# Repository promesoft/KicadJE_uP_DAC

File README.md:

# KicadJE_uP_DAC
Eurorack DAC output

# Purpose
Use for DDS/DCO - LFO - ADSR - Effects unit

# Status - Preliminary mounted
## Initial 
| Stage  | Detail | Status |
| ------------- | ------------- | ------------- |
| create material  | sch/pcb | OK  |
| | gerber | OK |
| production  |   | ok |
|  | produced | ok |
|  | delivered | ok |
## Preliminary validation
| Test  | Detail | Status |
| ------------- | ------------- | ------------- |
| Initial Inspection | | OK |
| Initial Technical Test | ATMega32A DAC | ADC not working due to GND conn to Aref |
| Initial Technical Test | STM32 DAC |  |
| Initial Technical Test | VCO555 | Initial version not oscillating - add 270R across C603 to make it work |
|  |  | TL074 warm |
| Initial Product Test | ATMega32A DAC |  |
| Initial Product Test | STM32 DAC |  |
| Initial Product Test | VCO555 |  |
| Power Draw | ATMega32A DAC | Proto - no DAC: 2mA -12V, 2mA +12V, 30mA +5V |
| Power Draw | STM32 DAC |  |
| Power Draw | VCO555 |  |

## Secondary validation
| Test  | Detail | Status |
| ------------- | ------------- |------------- |
| Product Test |  | |
| Product Test |  |  |
| Quality | | |
| Quality | | |
| Long Term Product Test |  |  |
| Power Draw | ATMega32A DAC |  |
| Power Draw | STM32 DAC |  |
| Power Draw | VCO555 |  |

## Errata
### Errata - VCO 555
1 - No oscillation fixed by replacing C603 w resistor (tested w 270R)
### Errata - ADSR Mega32
1 - ADC not working due to GND conn to Aref
### Errata - STM32 DAC

## Issues and Notes
### VCO 555

### ADSR Mega32
ADC not fast enough for audio

### STM32 DAC

# Pictures

# Other components

# Inspiration
## ATMega 32A
https://github.com/MCUdude/MightyCore
## STM32

## Simple 555 VCO

### Own Projects
https://github.com/promesoft/KicadFormantVCO

https://github.com/promesoft/KicadJE_LFO_1

### Intro about 555
https://www.electronics-tutorials.ws/waveforms/555_oscillator.html

### Thomas Henry 555 VCO

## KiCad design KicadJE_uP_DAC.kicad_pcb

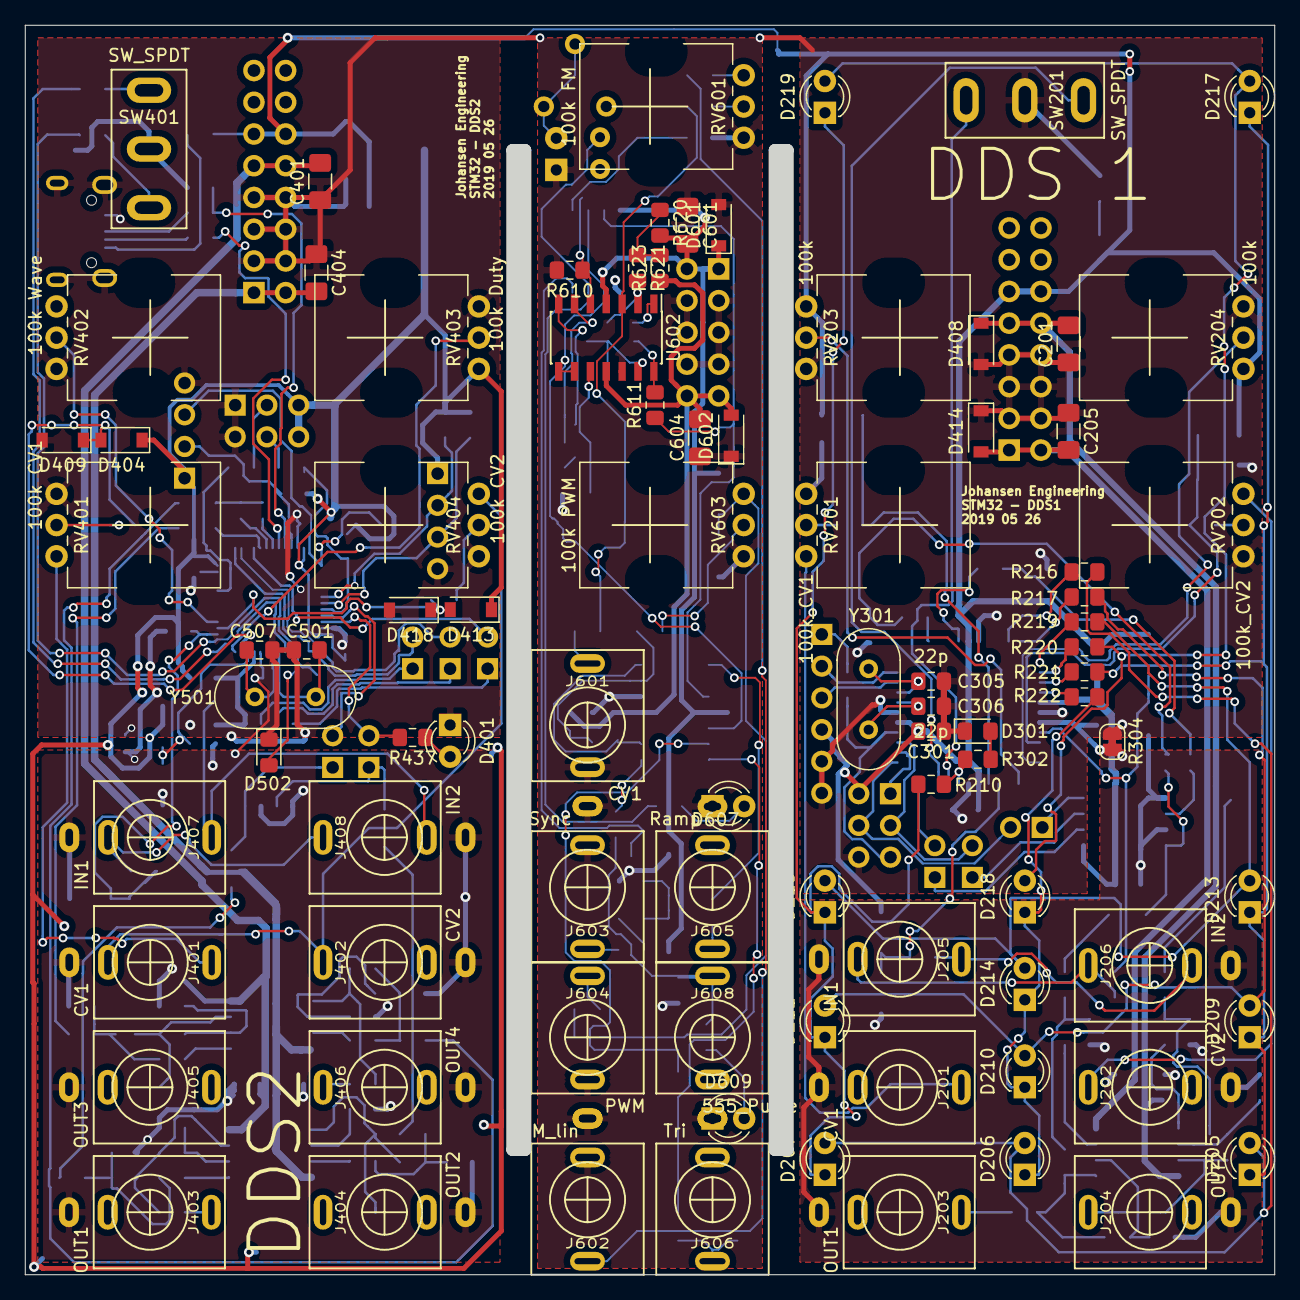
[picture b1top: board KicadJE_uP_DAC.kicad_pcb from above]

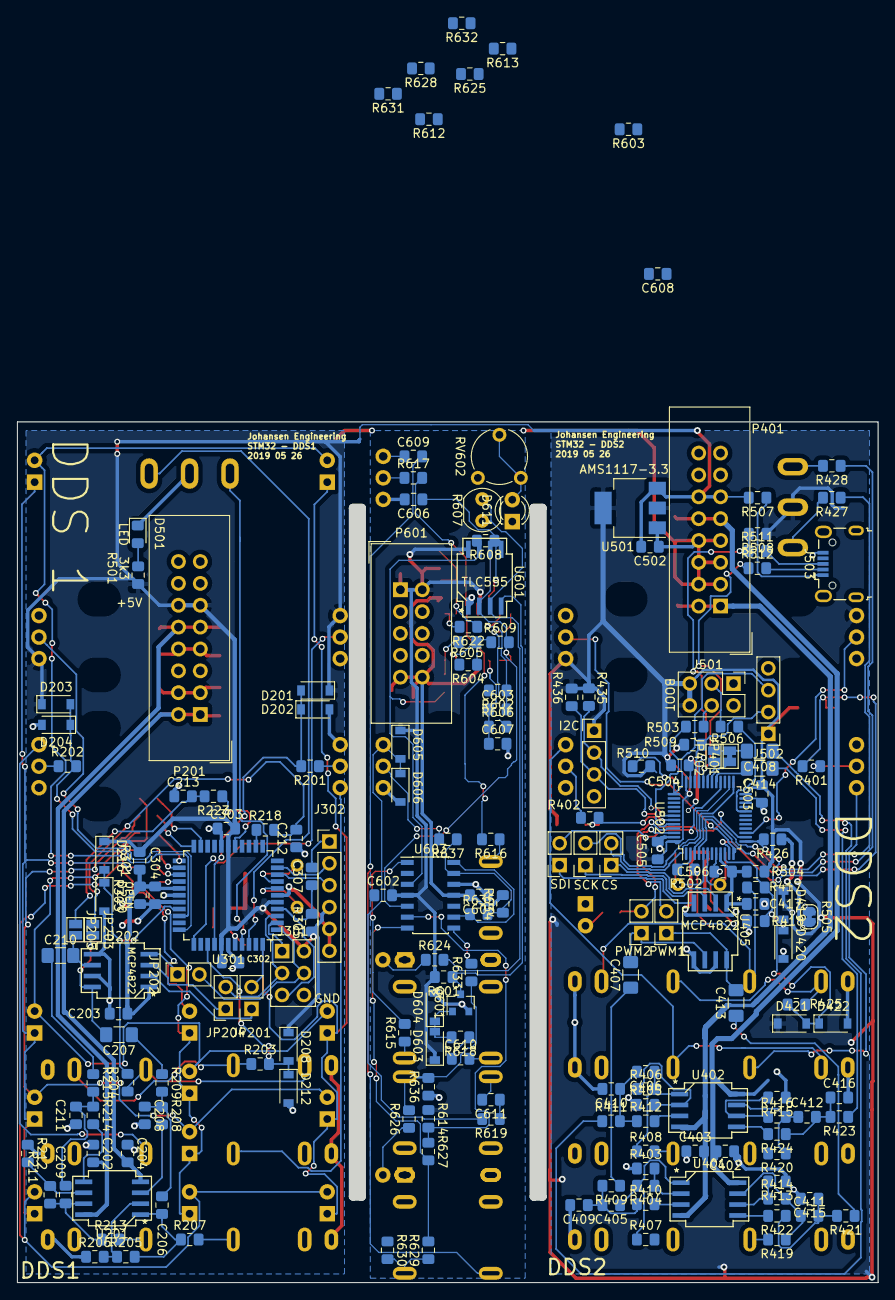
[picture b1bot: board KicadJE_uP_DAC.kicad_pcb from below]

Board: 2 copper layers, 100.0 x 100.0 mm, 275 parts (188 on the bottom side), 182 nets.

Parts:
C201, C205, C207, C210, C401, C404, C407, C408, C413, C414, C601, C604: 1u; C_1206_3216Metric_Pad1.42x1.75mm_HandSolder
C202, C203, C204, C206, C208, C209, C211, C212, C213, C301, C302, C303, C304, C307, C402, C403, C405, C406, C409, C410, C411, C412, C415, C416, C417, C503, C504, C505, C506, C602, C603, C605: 100n; C_0805_2012Metric_Pad1.15x1.40mm_HandSolder
C305, C306: 22p; C_0805_2012Metric_Pad1.15x1.40mm_HandSolder
C501, C507: 20p; C_0805_2012Metric_Pad1.15x1.40mm_HandSolder
C502: 470n; C_0805_2012Metric_Pad1.15x1.40mm_HandSolder
C606, C610, C611: 1n; C_0805_2012Metric_Pad1.15x1.40mm_HandSolder
C607: 22n; C_0805_2012Metric_Pad1.15x1.40mm_HandSolder
C608: 10n; C_0805_2012Metric_Pad1.15x1.40mm_HandSolder
C609: 220n; C_0805_2012Metric_Pad1.15x1.40mm_HandSolder
D201, D202, D203, D204, D208, D212, D216, D220, D404, D408, D409, D413, D414, D418, D419, D420, D421, D422, D601, D602, D603, D604, D605, D606: 1N1007; D_SOD-123
D205, D206, D207, D209, D210, D211, D213, D214, D215, D217, D218, D219, D401, D607, D609: LED; LED_D3.0mm
D301, D501, D502: LED; LED_0805_2012Metric_Pad1.15x1.40mm_HandSolder
D611: Vactrol; LED_D3.0mm
J201, J401, J601: CV1; PJ301SM
J202, J402: CV2; PJ301SM
J203, J403: OUT1; PJ301SM
J204, J404: OUT2; PJ301SM
J205, J407: IN1; PJ301SM
J206, J408: IN2; PJ301SM
J301: AVR-ISP-6; PinHeader_2x03_P2.54mm_Vertical
J302: UART; PinHeader_1x06_P2.54mm_Vertical
J405: OUT3; PJ301SM
J406: OUT4; PJ301SM
J409: I2C; PinHeader_1x04_P2.54mm_Vertical
J501: BOOT; PinHeader_2x03_P2.54mm_Vertical
J502: UART; PinHeader_1x04_P2.54mm_Vertical
J503: USB_B_Micro; USB_Micro-B_Wuerth_629105150521
J602: FM_lin; PJ301SM
J603: Sync; PJ301SM
J604: PWM; PJ301SM
J605: Ramp; PJ301SM
J606: Tri; PJ301SM
J608: 555_Pulse; PJ301SM
JP201: SS; PinSocket_1x02_P2.54mm_Vertical
JP202: MOSI; PinSocket_1x02_P2.54mm_Vertical
JP203: PWM1; SolderJumper-2_P1.3mm_Open_Pad1.0x1.5mm
JP204, JP404: SCK; PinSocket_1x02_P2.54mm_Vertical
JP205: PWM2; SolderJumper-2_P1.3mm_Open_Pad1.0x1.5mm
JP401: PA9; SolderJumper-2_P1.3mm_Bridged_Pad1.0x1.5mm
JP402: PA10; SolderJumper-2_P1.3mm_Open_Pad1.0x1.5mm
JP403: CS; PinSocket_1x02_P2.54mm_Vertical
JP405: SDI; PinSocket_1x02_P2.54mm_Vertical
JP406: PWM1; PinSocket_1x02_P2.54mm_Vertical
JP407: PWM2; PinSocket_1x02_P2.54mm_Vertical
P201, P401: Doepfer_Power_16pin; IDC-Header_2x08_Pitch2.54mm_Straight
P601: Doepfer_Power_10pin; IDC-Header_2x05_Pitch2.54mm_Straight
Q601: MMBT2222A; SOT-23
R201, R202, R203, R204, R205, R206, R208, R209, R211, R212, R214, R215, R305, R401, R402, R403, R404, R405, R406, R409, R410, R411, R412, R413, R414, R415, R416, R417, R418, R421, R422, R423, R424, R425, R426, R427, R428, R503, R506, R601, R611, R612, R613, R624, R626, R628: 10k; R_0805_2012Metric_Pad1.15x1.40mm_HandSolder
R207, R210, R213, R216, R217, R219, R220, R221, R222, R407, R408, R419, R420: 100R; R_0805_2012Metric_Pad1.15x1.40mm_HandSolder
R218, R223, R302, R615, R625: 1k; R_0805_2012Metric_Pad1.15x1.40mm_HandSolder
R301, R504: 0R; R_0805_2012Metric_Pad1.15x1.40mm_HandSolder
R303: OPEN; R_0805_2012Metric_Pad1.15x1.40mm_HandSolder
R304, R505: 0R; SolderJumper-2_P1.3mm_Bridged_RoundedPad1.0x1.5mm
R435, R436, R509, R510, R605, R609, R635, R637: 100k; R_0805_2012Metric_Pad1.15x1.40mm_HandSolder
R437: 820R; R_0805_2012Metric_Pad1.15x1.40mm_HandSolder
R501: 3k3; R_0805_2012Metric_Pad1.15x1.40mm_HandSolder
R502, R631: 2k2; R_0805_2012Metric_Pad1.15x1.40mm_HandSolder
R507, R511, R512: 10R; R_0805_2012Metric_Pad1.15x1.40mm_HandSolder
R508, R608: 1k5; R_0805_2012Metric_Pad1.15x1.40mm_HandSolder
R602: 12k; R_0805_2012Metric_Pad1.15x1.40mm_HandSolder
R603, R610, R616, R617, R618, R619: 47k; R_0805_2012Metric_Pad1.15x1.40mm_HandSolder
R604, R634: 150k; R_0805_2012Metric_Pad1.15x1.40mm_HandSolder
R606: 100r; R_0805_2012Metric_Pad1.15x1.40mm_HandSolder
R607: LDR03; R_LDR_4.9x4.2mm_P2.54mm_Vertical
R614, R627: 20k; R_0805_2012Metric_Pad1.15x1.40mm_HandSolder
R620, R623: 62k; R_0805_2012Metric_Pad1.15x1.40mm_HandSolder
R621, R622: 100k_test; R_0805_2012Metric_Pad1.15x1.40mm_HandSolder
R629, R630: 2k; R_0805_2012Metric_Pad1.15x1.40mm_HandSolder
R632: 2M2; R_0805_2012Metric_Pad1.15x1.40mm_HandSolder
R633: 3k; R_0805_2012Metric_Pad1.15x1.40mm_HandSolder
R636: 1k8; R_0805_2012Metric_Pad1.15x1.40mm_HandSolder
RV201: 100k_CV1; Potentiometer_China_RK09_Single_Vertical_AJ
RV202: 100k_CV2; Potentiometer_China_RK09_Single_Vertical_AJ
RV203, RV204: 100k; Potentiometer_China_RK09_Single_Vertical_AJ
RV401: 100k CV1; Potentiometer_China_RK09_Single_Vertical_AJ
RV402: 100k Wave; Potentiometer_China_RK09_Single_Vertical_AJ
RV403: 100k Duty; Potentiometer_China_RK09_Single_Vertical_AJ
RV404: 100k CV2; Potentiometer_China_RK09_Single_Vertical_AJ
RV601: 100k FM; Potentiometer_China_RK09_Single_Vertical_AJ
RV602: 5k; Potentiometer_Piher_PT-6-V_Vertical
RV603: 100k PWM; Potentiometer_China_RK09_Single_Vertical_AJ
SW201, SW401: SW_SPDT; SP1MS1
U201, U401, U402: TL072; AJ_SO-8_5.3x6.2mm_P1.27mm
U202, U405: MCP4822; AJ_SO-8_5.3x6.2mm_P1.27mm
U301: ATmega32A-AU; TQFP-44_10x10mm_P0.8mm
U501: AMS1117-3.3; SOT-223-3_TabPin2
U502: STM32F103C8Tx; LQFP-48_7x7mm_P0.5mm
U601: TLC555; AJ_SO-8_5.3x6.2mm_P1.27mm
U602, U603: TL074; SOIC-14_3.9x8.7mm_P1.27mm
Y301: 16MHz; Crystal_HC49-U_Vertical
Y501: 8 MHz; Crystal_HC49-U_Vertical

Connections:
32_0_LED: R210.1, R302.2, U301.40
32_1: SW201.3, U301.41
32_2_INT2: SW201.1, U301.42
32_4_SS_PWM: JP201.2, U301.44
32_5_MOSI: J301.4, JP202.2, U301.1
32_6_MISO: J301.1, U301.2
32_7_SCK: J301.3, JP204.2, U301.3
32_8_Rx: J302.3, U301.9
32_9_Tx: J302.2, U301.10
32_12_PWM: R218.1, U301.13
32_15_PWM: R223.1, U301.16
32_reset: C307.1, J301.5, R305.2, U301.4
555_CV: J601.T, R616.1
555_Dis: R611.1, U601.7, U603.3
555_FM: R617.1, RV601.2
555_In: R609.2, U601.2, U601.6, U602.8, U602.9, U603.5
555_Out: R607.2, R624.2, U601.3
555_PWM: D605.2, D606.1, R619.2, RV603.1
555_Pulse: J608.T, R626.2, R633.1, R636.2
555_Ramp: J605.T, R615.1
555_Sync: D603.2, D604.1, Q601.1, R618.2
555_Tri: J606.T, R629.1, R630.2
555_Tri_Direct: R627.2, R629.2, R631.2, U603.7
+3.3VA: C417.1, C506.2, R504.1, U405.1, U502.9
+3V3: C503.2, C504.2, C505.2, D404.1, D413.1, D419.1, D421.1, J409.1, J501.5, J501.6, J502.1, R435.2, R436.2, R504.2, R508.1, R509.2, R510.2, RV402.3, RV403.3, SW401.2, U501.2, U502.24, U502.36, U502.48
+5V: C301.2, C302.2, C303.2, C502.2, D201.1, D203.1, D208.1, D216.1, J301.2, J302.4, P201.11, P201.12, P401.11, P401.12, R301.2, R305.1, R501.2, R507.2, RV203.3, RV204.3, U301.5, U301.17, U301.38, U501.3
+5VA: C203.2, C304.2, R301.1, R303.1, U202.1, U301.27
+12V: C201.2, C202.2, C401.2, C402.2, C601.2, C602.2, D408.1, D601.1, D603.1, D605.1, P201.9, P201.10, P401.9, P401.10, P601.1, P601.2, R601.2, R603.1, R614.1, R620.2, U201.8, U401.8, U402.8, U601.8, U602.4, U603.4
-12V: C204.2, C205.2, C403.2, C404.2, C604.2, C605.2, D414.2, D602.2, P201.1, P201.2, P401.1, P401.2, P601.9, P601.10, R604.2, R623.1, R634.2, U201.4, U401.4, U402.4, U602.11, U603.11
/KicadJE_ATMega32A_DAC/1_inv: R205.1, R206.2, U201.2
/KicadJE_ATMega32A_DAC/1_noninv: R208.2, U201.3
/KicadJE_ATMega32A_DAC/1_out: C206.1, R205.2, R207.1, U201.1
/KicadJE_ATMega32A_DAC/2_inv: R211.1, R212.2, U201.6
/KicadJE_ATMega32A_DAC/2_noninv: R214.2, U201.5
/KicadJE_ATMega32A_DAC/2_out: C209.1, R211.2, R213.1, U201.7
/KicadJE_ATMega32A_DAC/ATMega32A.sch/18: R216.1, U301.21
/KicadJE_ATMega32A_DAC/ATMega32A.sch/19: R217.1, U301.22
/KicadJE_ATMega32A_DAC/ATMega32A.sch/20: R219.1, U301.23
/KicadJE_ATMega32A_DAC/ATMega32A.sch/21: R220.1, U301.24
/KicadJE_ATMega32A_DAC/ATMega32A.sch/22: R221.1, U301.25
/KicadJE_ATMega32A_DAC/ATMega32A.sch/23: R222.1, U301.26
/KicadJE_ATMega32A_DAC/SCK: JP204.1, U202.3
/KicadJE_ATMega32A_DAC/SDI: JP202.1, U202.4
/KicadJE_ATMega32A_DAC/SS: JP201.1, U202.2
/KicadJE_STM32F0/STM32F103C8/STM32_Boot0: R503.2, U502.44
/KicadJE_STM32F0/STM32F103C8/STM32_LED_PC13: R502.2, U502.2
/KicadJE_STM32F0/STM32F103C8/STM32_PB12: JP403.2, U502.25
/KicadJE_STM32F0/STM32F103C8/STM32_PB13: JP404.2, U502.26
/KicadJE_STM32F0/STM32F103C8/STM32_PB15: JP405.2, U502.28
/KicadJE_STM32F0/STM32F103C8/STM32_PC14: R427.1, U502.3
/KicadJE_STM32F0/STM32F103C8/STM32_PC15: R428.1, U502.4
/KicadJE_STM32F0/STM32F103C8/STM32_PWM_PA9: JP401.1, U502.30
/KicadJE_STM32F0/STM32F103C8/STM32_PWM_PA10: JP402.1, U502.31
/KicadJE_STM32F0/STM32F103C8/STM32_SCL1_PWM_PB8: JP406.2, U502.45
/KicadJE_STM32F0/STM32F103C8/STM32_SWCLK_PA14: J502.3, R510.1, U502.37
/KicadJE_STM32F0/STM32F103C8/STM32_SWDIO_PA13: J502.2, R509.1, U502.34
/KicadJE_STM32F0/STM32F103C8/STM32_USB_N_PA11: R512.1, U502.32
/KicadJE_STM32F0/STM32F103C8/STM32_USB_P_PA12: R508.2, R511.1, U502.33
/TH_555_VCO1/602invB: C603.2, R602.1, R603.2, U602.6
/TH_555_VCO1/602invD: R604.1, R605.2, R609.1, U602.13
/TH_555_VCO1/602outD: R605.1, R611.2, R612.1, U602.14
/TH_555_VCO1/603invD: R634.1, R635.2, R637.1, U603.13
/TH_555_VCO1/out603_1: R613.2, R615.2, U603.1
C0_22: D205.1, D209.1, D213.1, D217.1, R221.2
C1_23: D206.1, D210.1, D214.1, D218.1, R222.2
C2_0: D207.1, D211.1, D215.1, D219.1, R210.2
CV1: D201.2, D202.1, R201.2, U301.37
CV2: D203.2, D204.1, R202.2, U301.31
DACA: C207.2, JP203.2, U202.8
DACB: C210.2, JP205.2, U202.6
Duty: RV204.2, U301.33
GND: C201.1, C202.1, C203.1, C204.1, C205.1, C208.2, C211.2, C212.1, C213.1, C301.1, C302.1, C303.1, C304.1, C305.2, C306.2, C401.1, C402.1, C403.1, C404.1, C409.2, C410.2, C415.2, C416.2, C417.2, C501.2, C502.1, C503.1, C504.1, C505.1, C506.1, C507.2, C601.1, C602.1, C604.1, C605.1, C606.2, C607.2, C608.2, D202.2, D204.2, D212.2, D220.2, D301.1, D401.1, D408.2, D409.2, D414.1, D418.2, D420.2, D422.2, D501.1, D502.1, D601.2, D602.1, D604.2, D606.2, D607.1, D609.1, D611.1, J201.S, J202.S, J203.S, J204.S, J205.S, J206.S, J301.6, J302.5, J302.6, J401.S, J402.S, J403.S, J404.S, J405.S, J406.S, J407.S, J408.S, J409.4, J501.1, J501.2, J502.4, J503.5, J503.6, J601.S, J601.TN, J602.S, J602.TN, J603.S, J603.TN, J604.S, J604.TN, J605.S, J606.S, J608.S, P201.3, P201.4, P201.5, P201.6, P201.7, P201.8, P401.3, P401.4, P401.5, P401.6, P401.7, P401.8, P601.3, P601.4, P601.5, P601.6, P601.7, P601.8, Q601.2, R206.1, R212.1, R303.2, R304.1, R304.2, R403.1, R405.1, R413.1, R415.1, R418.1, R426.1, R505.1, R505.2, R602.2, R610.2, R628.1, R630.1, R636.1, RV201.3, RV202.3, RV203.1, RV204.1, RV401.3, RV402.1, RV403.1, RV404.3, RV601.3, RV603.3, SW201.2, U202.5, U202.7, U301.6, U301.18, U301.28, U301.29, U301.39, U405.5, U405.7, U501.1, U502.8, U502.23, U502.35, U502.47, U601.1, U602.12, U603.12
IN1: D208.2, D212.1, R203.2, U301.36
IN2: D216.2, D220.1, R204.2, U301.30
unnamed: C206.2, C208.1, R208.1, R209.2
unnamed: C207.1, R209.1
unnamed: C209.2, C211.1, R214.1, R215.2
unnamed: C210.1, R215.1
unnamed: C305.1, U301.8, Y301.1
unnamed: C306.1, U301.7, Y301.2
unnamed: C307.2, J302.1
unnamed: C405.1, R404.2, R407.1, U401.1
unnamed: C405.2, C409.1, R409.2, R410.1
unnamed: C406.1, R406.2, R408.1, U402.1
unnamed: C406.2, C410.1, R411.2, R412.1
unnamed: C407.1, R409.1
unnamed: C408.1, R411.1
unnamed: C411.1, R414.2, R419.1, U401.7
unnamed: C411.2, C415.1, R421.2, R422.1
unnamed: C412.1, R416.2, R420.1, U402.7
unnamed: C412.2, C416.1, R423.2, R424.1
unnamed: C413.1, R421.1
unnamed: C414.1, R423.1
unnamed: C501.1, U502.5, Y501.1
unnamed: C507.1, U502.6, Y501.2
unnamed: C603.1, C607.1, R606.1, U602.10
unnamed: C606.1, U601.5
unnamed: C608.1, R607.1, R608.2
unnamed: C609.1, RV601.1
unnamed: C609.2, J602.T
unnamed: C610.1, R618.1
unnamed: C610.2, J603.T
unnamed: C611.1, R619.1
unnamed: C611.2, J604.T
unnamed: D301.2, R302.1
unnamed: D401.2, R437.1
unnamed: D501.2, R501.1
unnamed: D502.2, R502.1
unnamed: D607.2, R624.1
unnamed: D609.2, R626.1
unnamed: D611.2, RV602.1, RV602.2
unnamed: J201.T, J202.TN, RV201.1
unnamed: J201.TN, J202.T, RV202.1
unnamed: J205.T, J206.TN, R203.1
unnamed: J205.TN, J206.T, R204.1
unnamed: J401.T, J402.TN, RV401.1
unnamed: J401.TN, J402.T, RV404.1
unnamed: J407.T, J408.TN, R417.1
unnamed: J407.TN, J408.T, R425.1
unnamed: J501.3, R506.1
unnamed: J503.1, R507.1
unnamed: J503.2, R512.2
unnamed: J503.3, R511.2
unnamed: JP403.1, U405.2
unnamed: JP404.1, U405.3
unnamed: JP405.1, U405.4
unnamed: Q601.3, R601.1, U601.4
unnamed: R201.1, RV201.2
unnamed: R202.1, RV202.2
unnamed: R401.1, RV401.2
unnamed: R402.1, RV404.2
unnamed: R403.2, R404.1, U401.2
unnamed: R405.2, R406.1, U402.2
unnamed: R410.2, U401.3
unnamed: R412.2, U402.3
unnamed: R413.2, R414.1, U401.6
unnamed: R415.2, R416.1, U402.6
unnamed: R422.2, U401.5
unnamed: R424.2, U402.5
unnamed: R427.2, SW401.3
unnamed: R428.2, SW401.1
unnamed: R606.2, U602.7
unnamed: R608.1, R610.1, U602.5
unnamed: R612.2, R613.1, U603.2
unnamed: R614.2, R627.1, R628.2, U603.6
unnamed: R620.1, R621.1, R623.2
unnamed: R621.2, R622.1, U602.2
unnamed: R622.2, R625.2, U602.1
unnamed: R625.1, RV602.3
unnamed: R631.1, R632.2, U603.10
unnamed: R632.1, R633.2, U603.8
unnamed: R635.1, U603.9, U603.14
unnamed: R637.2, RV603.2
OUT1: J203.T, R207.2
OUT2: J204.T, R213.2
PB2_R2: R506.2, U502.20
PB6_SCL1: J409.2, R435.1, U502.42
PB7_SDA1: J409.3, R436.1, U502.43
PB9_PWM: JP407.2, R437.2, U502.46
PWM12: C212.2, JP203.1, R218.2
PWM15: C213.2, JP205.1, R223.2
PWM_PA8: C414.2, U502.29
PWM_PA9: C408.2, JP401.2, JP402.2
R0_18: D205.2, D206.2, D207.2, R216.2
R1_19: D209.2, D210.2, D211.2, R217.2
R2_20: D213.2, D214.2, D215.2, R219.2
R3_21: D217.2, D218.2, D219.2, R220.2
STM32_CV1: D404.2, D409.1, R401.2, U502.11
STM32_CV2: D413.2, D418.1, R402.2, U502.14
STM32_Duty: RV403.2, U502.12
STM32_IN1: D419.2, D420.1, R417.2, R418.2, U502.10
STM32_IN2: D421.2, D422.1, R425.2, R426.2, U502.13
STM32_OUT1: J403.T, R419.2
STM32_OUT2: J404.T, R407.2
STM32_OUT3: J405.T, R420.2
STM32_OUT4: J406.T, R408.2
STM32_Wave: RV402.2, U502.15
STM_DACA: C413.2, JP406.1, U405.8
STM_DACB: C407.2, JP407.1, U405.6
VCO_Control: R616.2, R617.2, U602.3
Wave: RV203.2, U301.34
boot_0: J501.4, R503.1

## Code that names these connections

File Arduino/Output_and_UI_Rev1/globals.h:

#ifndef GLOBALS_H
#define GLOBALS_H

#include <stdint.h> // For uint8_t

//LEDs
#define row0 18
#define row1 19
#define row2 20
#define row3 21
#define col0 0
#define col1 22
#define col2 23

//Switch
#define rightsel 1 //Digital pin for right select
#define leftsel 2 //Digital pin for left select

//POTs
#define topleft A3  // Wave = A3 = 27 = PA3
#define topright A4 // Duty = A4 = 28 = PA4

//CV
#define leftcv A0  // left = A0 = 24 = PA0 - J201 CV1 - left in
#define rightcv A6 // right = A6 = 30 = PA6 - J202 CV2 - right in
extern int right_cv, left_cv;

//Output
#define leftout 12  // left = 12 - J203 OUT1 - PWM12/DACA - left out
#define rightout 15 // right = 15 - J204 OUT2 - PWM15/DACB - right out

//Input
#define leftin A1  // left = A1 = 25 = PA1 - J205 IN1 - left in
#define rightin A7 // right = A7 = 31 = PA7 - J206 IN2 - right in
extern int right_in, left_in;

extern int sw_state; // What should the pot's do? 0 = Left 1 = Right 2 = Center 
// Right/Left
// Top - show which side is selected
// Input - Bank 1 (sine, half sine, sine^2, Sharkfin)
// CV - Bank 2 (Saw, inv Saw, tri, saw+inv saw)
// Output - Bank 3 (Square 10%, 25%, 10%..40%, noise)
// Center shows selected waveform (1,2,3,4)
// Pot left selects bank
// Pot right selects waveform

// Center 
// L/R Input - CV - Output - shows value over 511 
// L/R Output - shows value over 127
// Center shows ??
// Pot left selects left pause (duty)
// Pot right selects right pause (duty)


// Used to differ between changing states. If the last val was close to the new val - dont change.
extern unsigned int old_left, left_potval;
extern unsigned int old_right, right_potval;

extern unsigned int left_bank;
extern unsigned int left_wave;
extern unsigned int left_duty;
extern unsigned int left_shape;
extern unsigned int left_out;
extern unsigned int right_bank;
extern unsigned int right_wave;
extern unsigned int right_shape;
extern unsigned int right_duty;
extern unsigned int right_out;
extern unsigned int waveform;

extern int LEDColPin[3]; // Left Right Center 
extern int LEDRowPin[4]; // bottom...top
extern bool LEDData[3][4]; // Left Center Right
extern bool left_sel, right_sel;

extern unsigned long lastLwaveupdate,lastRwaveupdate,lastupdate;
extern uint8_t tableLStep, tableRStep;
#endif

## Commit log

2019-05-18 Add Delay Line effect
    Add delay line
    Probable addition:
    Encoder or Pot to decide
    -delay time
    -tap's
    -digital feedback
2019-05-18 Sch resumed from ADSR Atmega32
2019-05-18 MCP4822
2019-05-19 Hierarchical ATMega32 pins
2019-05-19 Ardiono lib initiated
2019-05-19 2x Sallen Key LP out from DAC
2019-05-19 CV and Input protection
2019-05-19 LED Matrix 3x4
2019-05-20 Dual uP hierarchy
2019-05-20 STM32F103C8
2019-05-20 USB - Boot sel - Serial - STM32
2019-05-20 STM32 DAC and Analog input
2019-05-20 POT GND
2019-05-21 STM32 Pin names for serial and USB
2019-05-21 Multiple updates - Initial PCB
    Footprint updates
    LED updates
2019-05-21 Intersheet cleanup
    Footprints and cleanup naming on global labels between sheets
2019-05-21 LED Matrix ATMega32 rename
2019-05-21 Sch cleanup and sorting of components in ATMega
2019-05-22 LED and Xtal
2019-05-22 ATMega 32 placed again - decoupling added
2019-05-22 +5V ATMega
2019-05-22 12V PWR
2019-05-22 Routed
2019-05-23 STM32 Initiated layout
2019-05-23 Primary components
2019-05-23 Power routed
2019-05-23 Connectors arount STM32
2019-05-25 serial to DAC - STM32
2019-05-25 Changed Op Amp A and B
2019-05-25 Output filter routing STM32
2019-05-25 MCP to GNDA and 3.3VA
2019-05-25 Missing Column Driver for column 2 - STM32
2019-05-25 I'll probably have to skip the LED array
2019-05-25 tweaking vias and routing around STM32
2019-05-25 Diode protection - STM32
2019-05-25 STM32 routed without LED's
2019-05-26 Diode etc
2019-05-26 ERC Performed
2019-05-26 Before ERC Netlist
2019-05-26 Silk update - DDS1 and DDS2 routed
2019-05-26 TH 555 Sheet initiated
2019-05-27 555 Core VCO Schematic
2019-05-27 Sch for 555 VCO - Core - Sync - Tri - Ramp done
2019-05-29 555 Tri Ramp Pulse
2019-05-29 before sine
2019-05-29 Before Sine PCB on 555
2019-05-30 16p -> 10p on 555 VCO
2019-05-30 555 PCB
2019-05-30 Placing outputs and Pots 555
2019-05-30 555 Pwr to U603
2019-05-30 555 Power routed
2019-05-30 Labels mixup
2019-05-30 555 flip
2019-05-30 Most components placed 555
2019-05-30 555 Routed
2019-05-30 label sch + png
2019-05-30 555 sch boxes
2019-05-30 Label done
2019-05-31 ERC Done
2019-05-31 Gerber Rev A done
2019-10-15 RevB initiated
2019-10-15 Doepfer power conn reversed :o
2020-04-10 minor
2020-04-11 blinks
2020-04-11 Create test_POTS_n_LED.ino
    Making a bit of structure
2020-04-14 Update Initial_UI.ino
    Print statements - programming via USBasp and monitoring via serial
2020-04-14 Update Initial_UI.ino
    I/O labels and pinout
2021-05-13 Kicad 5.1
2021-05-13 STM32 sch
2024-12-25 update
    update
